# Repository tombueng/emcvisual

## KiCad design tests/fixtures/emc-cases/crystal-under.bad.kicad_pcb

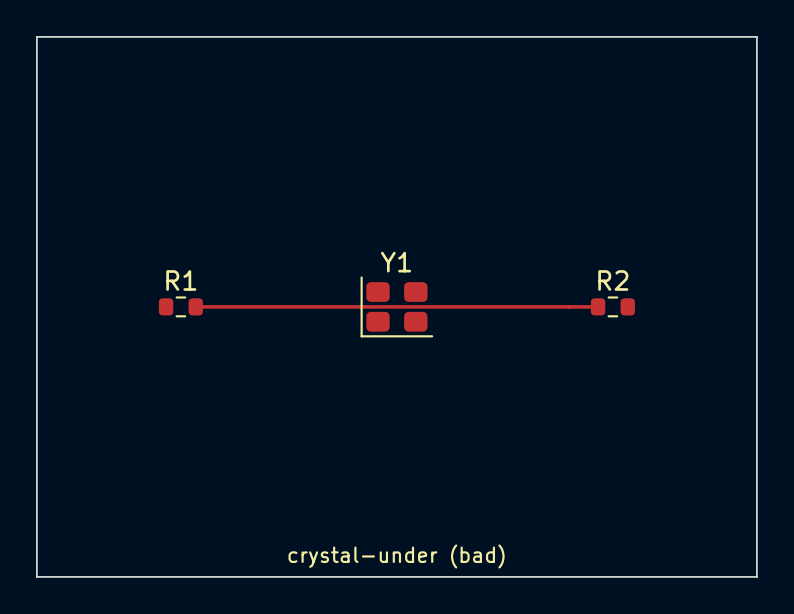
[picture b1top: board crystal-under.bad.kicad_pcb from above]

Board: 2 copper layers, 40.0 x 30.0 mm, 3 parts (0 on the bottom side), 3 nets.

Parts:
R1, R2: 1k; R_0603_1608Metric
Y1: 25MHz; Oscillator_SMD_Abracon_ASE-4Pin_3.2x2.5mm

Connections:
+3V3: R1.2, Y1.1, Y1.4
GND: R2.2, Y1.2
LED: R1.1, R2.1

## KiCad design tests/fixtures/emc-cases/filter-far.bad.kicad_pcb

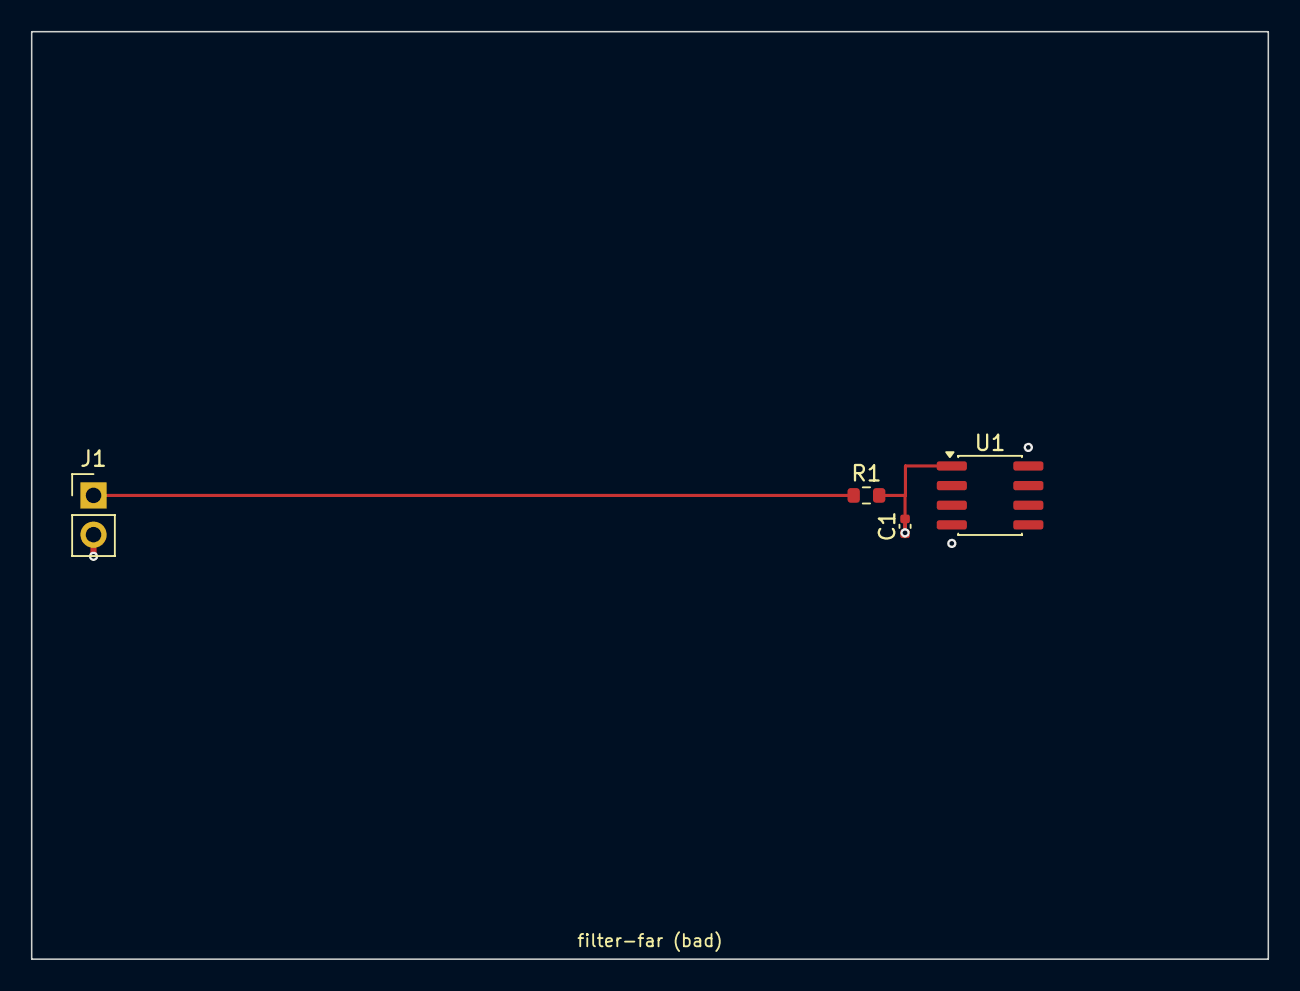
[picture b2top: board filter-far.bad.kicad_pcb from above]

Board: 4 copper layers, 80.0 x 60.0 mm, 4 parts (0 on the bottom side), 3 nets.

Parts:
C1: 1nF; C_0402_1005Metric
J1: IO; PinHeader_1x02_P2.54mm_Vertical
R1: 100R; R_0603_1608Metric
U1: MCU; SOIC-8_3.9x4.9mm_P1.27mm

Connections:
GND: C1.2, J1.2, U1.4
IO_IN: J1.1, R1.1
IO_U: C1.1, R1.2, U1.1
